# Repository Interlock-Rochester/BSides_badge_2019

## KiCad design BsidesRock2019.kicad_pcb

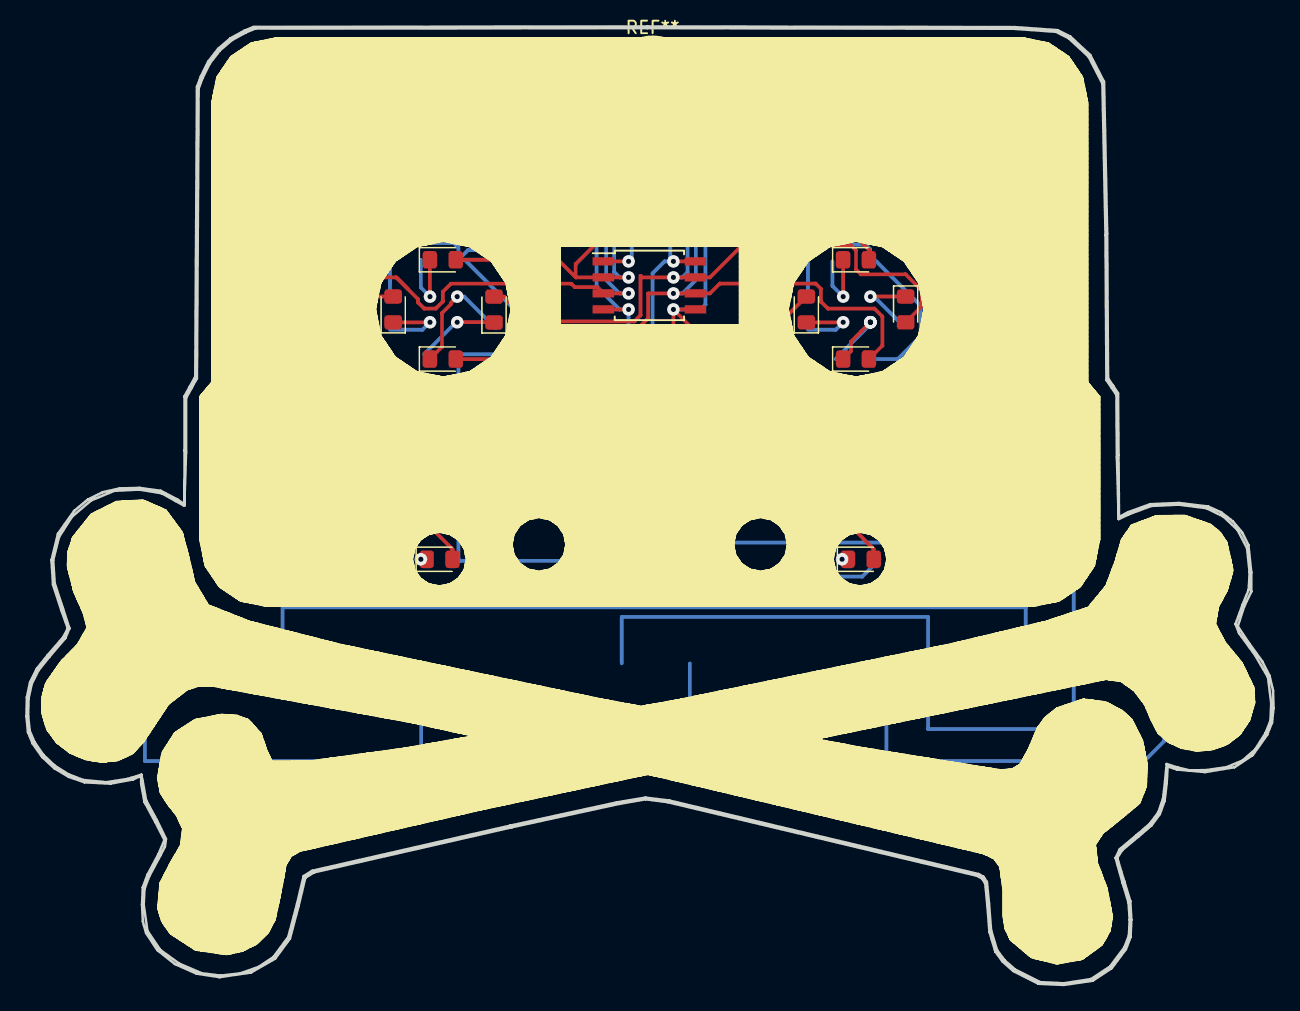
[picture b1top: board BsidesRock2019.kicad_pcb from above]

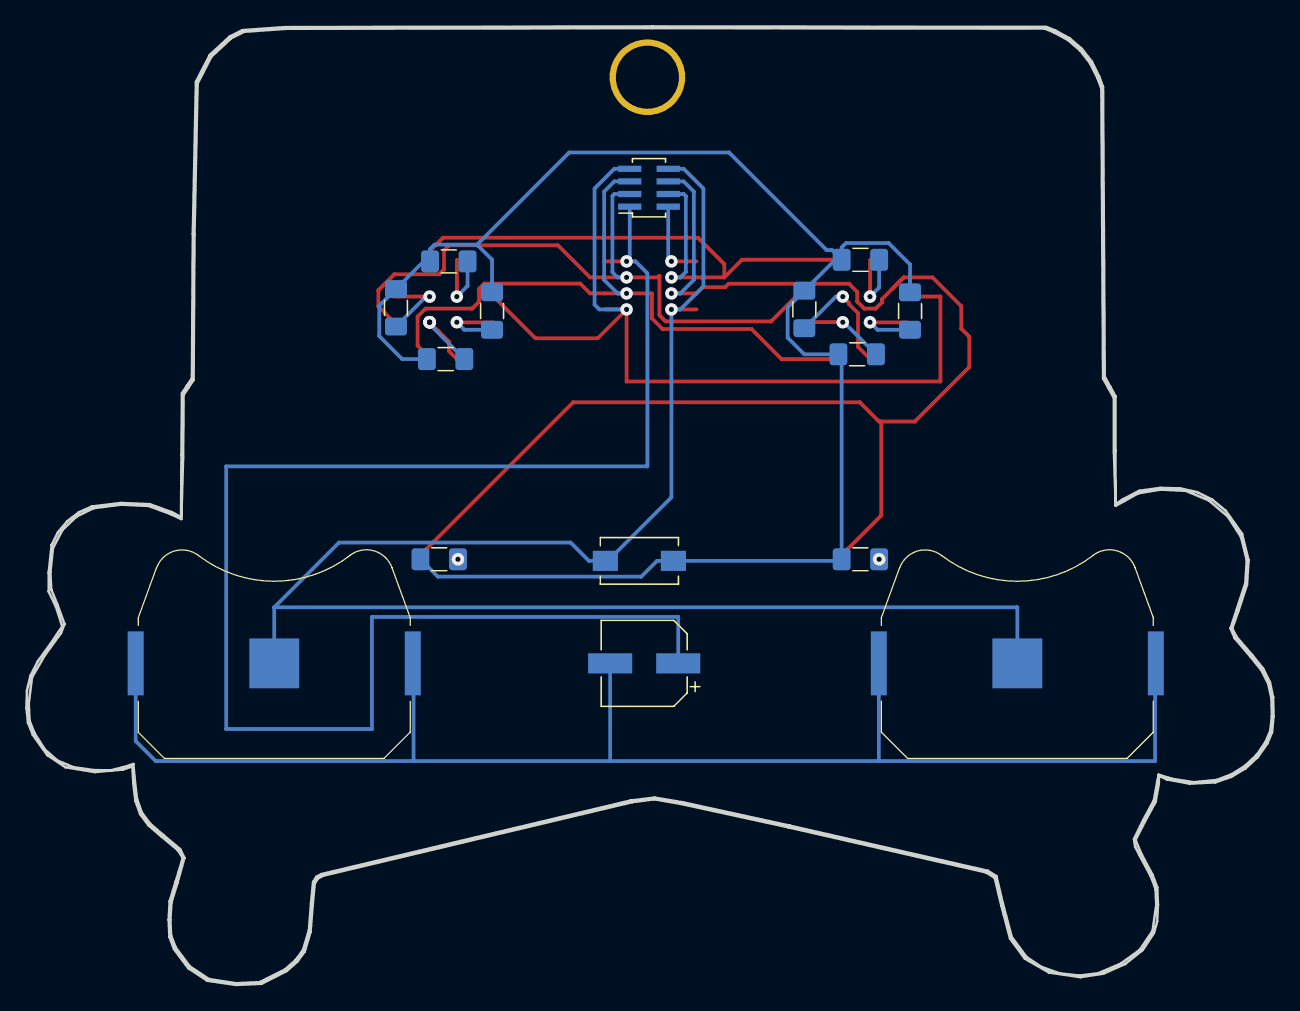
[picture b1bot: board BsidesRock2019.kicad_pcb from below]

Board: 2 copper layers, 98.9 x 76.0 mm, 26 parts (15 on the bottom side), 20 nets.

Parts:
BT-2032-1, BT-2032-2: Battery_Cell; BatteryHolder_Keystone_3034_1x20mm
C100uF1: CP1_Small; CP_Elec_6.3x5.4_Nichicon
D1, D2, D3, D4, D5, D6, D7, D8, D9, D10: LED; LED_0805_2012Metric_Pad1.15x1.40mm_HandSolder
JPROGHEADER1: Conn_01x08_Male; PinSocket_2x04_P1.00mm_Vertical_SMD
R56-Ohm1, R56-Ohm2, R56-Ohm3, R56-Ohm4, R56-Ohm5, R56-Ohm6, R56-Ohm7, R56-Ohm8, R56-Ohm9, R56-Ohm10: R_Small; R_1206_3216Metric_Pad1.42x1.75mm_HandSolder
SW-LEDGROUND1: SW_SPST; SW_SPST_EVQPE1
U1: ATtiny85V-10SU; SOIJ-8_5.3x5.3mm_P1.27mm

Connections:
unnamed: BT-2032-1.1, BT-2032-2.1, C100uF1.2
unnamed: BT-2032-1.2, BT-2032-2.2, JPROGHEADER1.8, SW-LEDGROUND1.2, U1.4
unnamed: C100uF1.1, JPROGHEADER1.1, U1.8
unnamed: D1.1, R56-Ohm1.1
unnamed: D1.2, D6.2, JPROGHEADER1.7, U1.5
unnamed: D2.1, R56-Ohm4.1
unnamed: D2.2, D9.2, JPROGHEADER1.6, U1.3
unnamed: D3.1, R56-Ohm3.1
unnamed: D3.2, D7.2, JPROGHEADER1.4, U1.2
unnamed: D4.1, R56-Ohm2.1
unnamed: D4.2, D8.2, JPROGHEADER1.5, U1.6
unnamed: D5.1, R56-Ohm5.1
unnamed: D6.1, R56-Ohm7.1
unnamed: D7.1, R56-Ohm8.1
unnamed: D8.1, R56-Ohm9.1
unnamed: D9.1, R56-Ohm6.1
unnamed: D10.1, R56-Ohm10.1
unnamed: D5.2, D10.2, JPROGHEADER1.3, U1.7
unnamed: JPROGHEADER1.2, U1.1
unnamed: R56-Ohm1.2, R56-Ohm2.2, R56-Ohm3.2, R56-Ohm4.2, R56-Ohm5.2, R56-Ohm6.2, R56-Ohm7.2, R56-Ohm8.2, R56-Ohm9.2, R56-Ohm10.2, SW-LEDGROUND1.1

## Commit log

2018-11-12 Prototype 01
2018-11-20 Add files via upload
    updated routes to pwn pins and ordered designs
